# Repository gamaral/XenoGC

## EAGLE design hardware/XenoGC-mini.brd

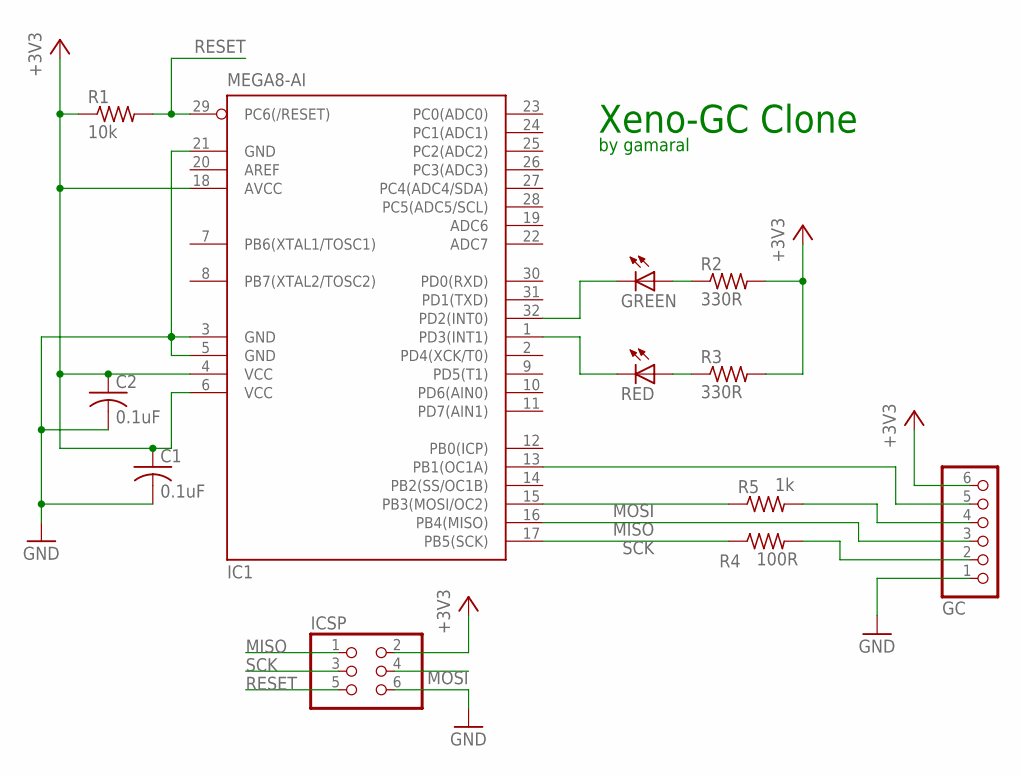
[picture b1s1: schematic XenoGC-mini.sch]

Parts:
C1, C2: 0.1uF; C0805K
GC: PINHD-1X6/90; 1X06/90
GREEN: LEDSML1206; SML1206
IC1: MEGA8-AI; TQFP32-08
ICSP: PINHD-2X3; 2X03
R1: 10k; R0805W
R2, R3: 330R; R0805W
R4: 100R; R0805W
R5: 1k; R0805W
RED: LEDSML1206; SML1206

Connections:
+3V3: C1.1, C2.1, GC.6, IC1.4 (VCC), IC1.6 (VCC), IC1.18 (AVCC), ICSP.2, R1.1, R2.2, R3.2
GC2: GC.2, R4.2
GC3: GC.4, R5.2
GND: C1.2, C2.2, GC.1, IC1.3 (GND), IC1.5 (GND), IC1.21 (GND), ICSP.6
LED1: GREEN.C, IC1.32 (PD2(INT0))
LED2: IC1.1 (PD3(INT1)), RED.C
MISO: GC.3, IC1.16 (PB4(MISO)), ICSP.1
MOSI: IC1.15 (PB3(MOSI/OC2)), ICSP.4, R5.1
unnamed: GREEN.A, R2.1
unnamed: R3.1, RED.A
PB1: GC.5, IC1.13 (PB1(OC1A))
RESET: IC1.29 (PC6(/RESET)), ICSP.5, R1.2
SCK: IC1.17 (PB5(SCK)), ICSP.3, R4.1

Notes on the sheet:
Xeno-GC Clone
by gamaral

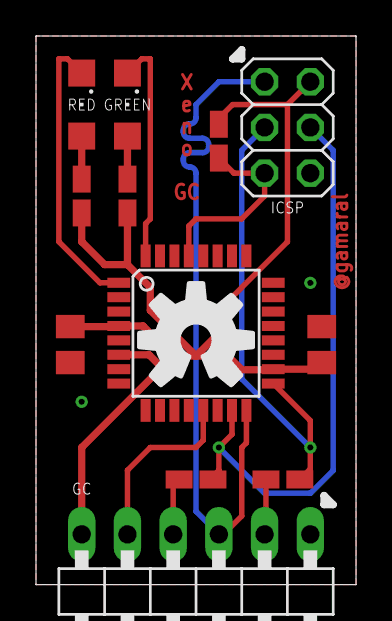
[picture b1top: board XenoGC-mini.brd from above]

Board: 2 copper layers, 17.8 x 30.5 mm, 12 parts (0 on the bottom side), 13 nets.

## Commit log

2013-09-19 Added Xeno-GC Mini!
